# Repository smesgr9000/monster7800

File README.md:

# Alternative Atari 7800 compatible PCB for Monster Joystick Retro Kits

monster7800 is an alternative PCB board for the Monster Joysticks 8/16bit *Retro BASIC* and *Deluxe* Joystick Kits to support both buttons on Atari 7800 console. The board also works with some other devices, like the original Atari 7800 Proline joystick and gamepad.

*This project is not associated with Monster Joysticks Ltd.*

## ordering boards

To order the latest version either use KiCad or use release zip from GitHub.
To generate the Gerber files yourself, open _monster7800.kicad_pcb_ in KiCad. Use _Fabrication Output_ > _Gerber_ and select an output folder and agree with _Plot_ with the default configruation. Also use _Fabrication Output_ > _Drill Files_ than select the same output folder and agree with _Generate Drill File_.

The ordering and manufacturing depends on your selected PCB manufacturer. For www.pcbway.com:

- enter length/width (57 x 33mm)
- 2 layers
- 1.6mm thickness
- FR4
- TG 150-160
- 6/6mil Min Tracking
- 0.3mm Hole Size
- Solder Mask - any is fine
- Silkscreen - any is fine
- No Edge Connector
- Finish - any is fine but would suggest HASL
- Tending Vias
- 1oz Finish Copper

Upload a zip containing the above generated files. Currently the price for 5 boards should be 5$.

## soldering

To finish the board two resistors are required. You could reuse and desolder the D-Sub 9 connector and pin header of the shipped Joystick Kit thus marked optional in the list below.

Reference | Part | Amount | Description
--- | --- | --- | ---
R1, R2 | Vishrey MRS25000C6200FCT00 | 2 | 620ohm resistor
J1 | Amphenol 10129379-909004BLF | 1 | optional, if Joystick Kit pin header isn't reused
J2 | Amphenol  D09S33E4GV00LF | 1  | optional, if Joystick Kit D-Sub isn't reused

## building

if the joystick isn't build yet, follow the building instruction of the joystick and use the monster7800 instead of the delivered board. Otherwise open up the top cover and replace the current PCB board with the atari7800.

## compatibility

As the original Atari 7800 joystick a Monster Joystick equipped with this PCB should have the same compatibility list. Some tested devices:

Device | Works | Description
--- | --- | ---
Atari 7800 | Yes | PAL & NTSC tested, buttons could be flipped see original build instructions
Atari 2600 | Yes | PAL Jr tested, both buttons are recognised, but 2600 only support one action
Atari 8bit | Yes | PAL 800XL tested, both buttons are recognised, but computer only support one action
Atari ST | Depends | STE tested, does not work in mouse port (port 0), works fine in joystick port (port 1)

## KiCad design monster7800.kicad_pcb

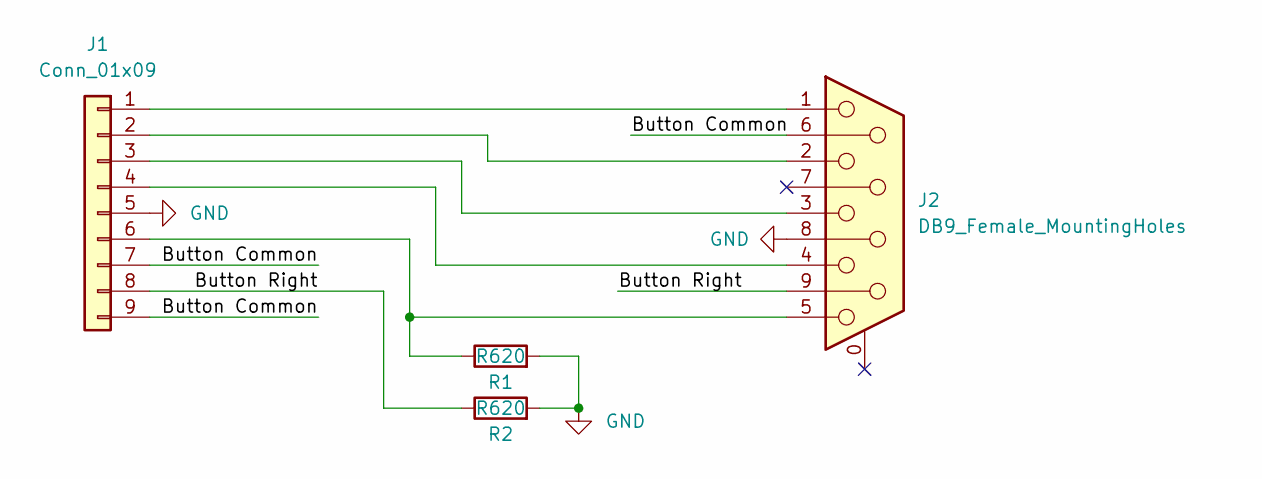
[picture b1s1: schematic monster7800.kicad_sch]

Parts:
J1: Conn_01x09; PinHeader_1x09_P2.54mm_Vertical
J2: DB9_Female_MountingHoles; DSUB-9_Female_Horizontal_P2.77x2.84mm_EdgePinOffset4.94mm_H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
R1, R2: R620; R_Axial_DIN0309_L9.0mm_D3.2mm_P12.70mm_Horizontal

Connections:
/Button Common: J1.7, J1.9, J2.6
/Button Right: J1.8, J2.9, R2.1
GND: J1.5, J2.8, R1.2, R2.2
unnamed: J1.1, J2.1
unnamed: J1.2, J2.2
unnamed: J1.3, J2.3
unnamed: J1.4, J2.4
unnamed: J1.6, J2.5, R1.1

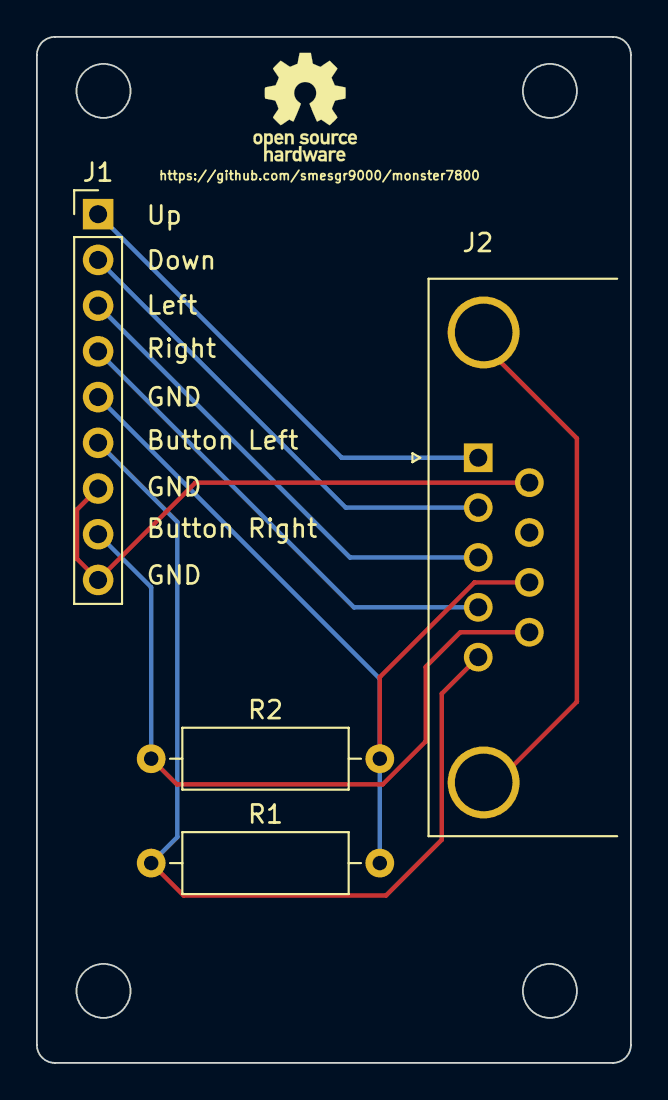
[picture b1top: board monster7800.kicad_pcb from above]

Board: 2 copper layers, 33.0 x 57.0 mm, 4 parts (0 on the bottom side), 8 nets.

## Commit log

2023-11-11 add more information how to build and order
2023-11-11 fix tables
2023-11-11 add reference to github page on PCB
2023-11-11 add picture and info about relation to ltd
2023-11-11 fix last
2023-11-11 Update README.md
    either use provided Gerber or use Release
2024-12-20 update to Kicad 8
